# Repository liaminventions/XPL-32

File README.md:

# XPL-32

The XPL-32 is a homebrew 8-bit 6502 laptop, with four 48-pin expansion slots, and a 22-pin I/O port.
 ### XPL-32 stands for:
e**X**pandable 
**P**ersonal 
**L**aptop 
with **32**k ram
# [Blog](https://unstinkableinventions.wordpress.com/)
Here I will post hardware updates to the XPL and more.

Also, be sure to check info.txt to know if there are any issues when i code.
# Hardware Overview
## CPU
A 6502, of course. A W65C02 to be exact. 

[Datasheet](https://eater.net/datasheets/w65c02s.pdf)
## I/O
For the I/O, I've got a W65C22 VIA. Port A, Port B and the handshake bits connect to the I/O slot.
However CA2 is connected to the Video Switch Relay (VSR)
[W65C22 Datasheet](https://eater.net/datasheets/w65c22.pdf)
## Video
The XPL-32 has an expandable monochrome terminal display that uses a 6551 ACIA  at $8000 and two arduinos.
[This is the video and keyboard processer. (not made by me)](http://searle.x10host.com/MonitorKeyboard/index.html)
The video can be switched to the composite input EXTVID (on the expansion port) by toggling the VSR. (a relay that switches beetween native video and EXTVID.)

So far, for Video expansions, I've made a TMS9918a one. (the same video processer used in the TI-99/4a and the MSX)
## Sound
There is a 6581 SID at $B800 ($D400 in the c64) onboard with its potentiometer (POTX and POTY) and external sound (EXTSND) inputs on the expansion port.
I programmed support to convert most SID files, as well.
# Memory Map

# Tools I Use
## PCB Design
I currently use [EAGLE](https://www.autodesk.com/products/eagle/free-download)
## 3D Modeling
[Fusion 360](https://www.autodesk.com/products/fusion-360/overview?us_oa=dotcom-us&us_si=4e5471dc-07ed-4416-80c0-6f3e9f7c15b4&us_pt=NINVFUS&us_at=%5Bobject%20Object%5D&term=1-YEAR&tab=subscription&plc=F360)
## Coding
[VIM](https://www.vim.org/), [NVIM](https://neovim.io/)/[LunarVIM](https://www.lunarvim.org/) or [vscode](https://code.visualstudio.com/) for code editing.
[xa](https://github.com/fachat/xa65), [ca65](https://github.com/cc65/cc65) (from cc65), and [vasm](http://sun.hasenbraten.de/vasm/) for assembly.

I have "xa 6502 cross assembler" syntax highlighting in vim, and the "vasm" extension in vscode.

most source files are .s, but some are .a65 or .asm

## Debugging 

I use [Pulseview](https://sigrok.org/wiki/PulseView) with [this logic analyzer (the 2018 variant)](https://sigrok.org/wiki/Mcupro_Logic16_clone)

It was an absolute pain to set up...

Also, the SDcard-SPI decoder in libsigrokdecode was completly broken for me. (it always expected a CRC...) My fix was to make [my own custom version of the decoder](https://github.com/liaminventions/XPL-32/tree/main/debug/decoders/sdcard_spi)

The custom version is still slightly broken, but I am working on it.

I also use [decode6502 by hoglet](https://github.com/hoglet67/6502Decoder)

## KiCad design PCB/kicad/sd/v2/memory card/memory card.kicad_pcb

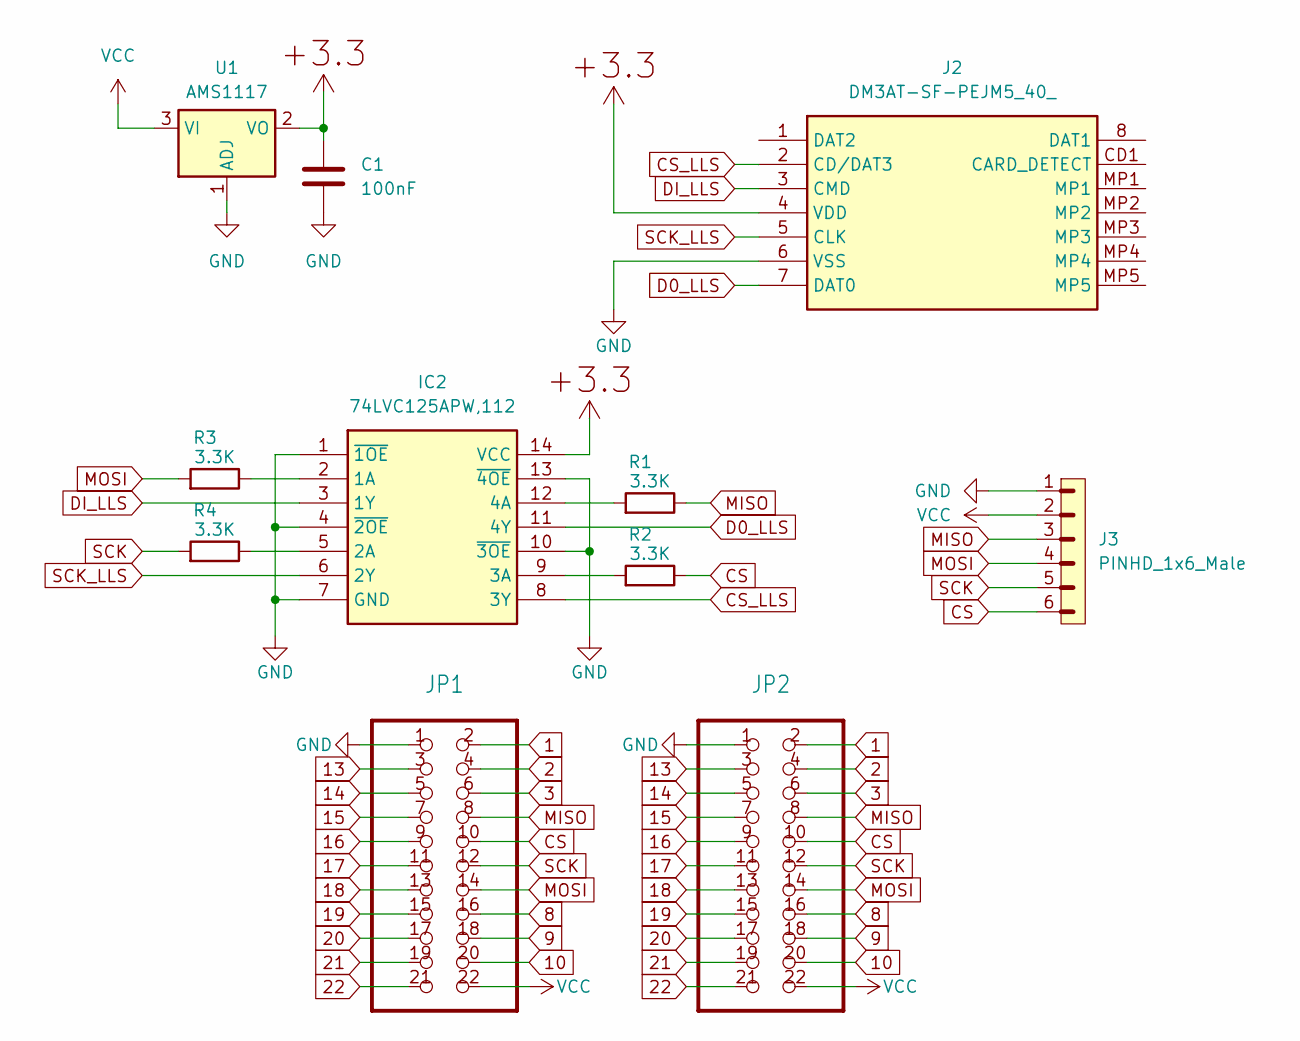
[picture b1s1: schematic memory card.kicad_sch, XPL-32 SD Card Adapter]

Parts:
C1: 100nF; C_0603_1608Metric
IC2: 74LVC125APW,112; SOP65P640X110-14N; Mouser2 Part Number 771-LVC125APW112
J2: DM3AT-SF-PEJM5_40_; DM3ATSFPEJM540; Mouser Part Number 798-DM3AT-SF-PEJM540
J3: PINHD_1x6_Male; PinHeader_1x06_P2.54mm_Vertical
JP1, JP2: 2X11_90_325
R1, R2, R3, R4: 3.3K; R_0805_2012Metric
U1: AMS1117; SOT-223-3_TabPin2

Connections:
1: JP1.2, JP2.2
2: JP1.4, JP2.4
3: JP1.6, JP2.6
8: JP1.16, JP2.16
9: JP1.18, JP2.18
10: JP1.20, JP2.20
13: JP1.3, JP2.3
14: JP1.5, JP2.5
15: JP1.7, JP2.7
16: JP1.9, JP2.9
17: JP1.11, JP2.11
18: JP1.13, JP2.13
19: JP1.15, JP2.15
20: JP1.17, JP2.17
21: JP1.19, JP2.19
22: JP1.21, JP2.21
CS: J3.6, JP1.10, JP2.10, R2.2
CS_LLS: IC2.8 (3Y), J2.2 (CD/DAT3)
D0_LLS: IC2.11 (4Y), J2.7 (DAT0)
DI_LLS: IC2.3 (1Y), J2.3 (CMD)
GND: C1.2, IC2.1 (~1OE), IC2.4 (~2OE), IC2.7 (GND), IC2.10 (~3OE), IC2.13 (~4OE), J2.6 (VSS), J3.1, JP1.1, JP2.1, U1.1 (ADJ)
MISO: J3.3, JP1.8, JP2.8, R1.2
MOSI: J3.4, JP1.14, JP2.14, R3.1
unnamed: IC2.2 (1A), R3.2
unnamed: IC2.5 (2A), R4.2
unnamed: IC2.9 (3A), R2.1
unnamed: IC2.12 (4A), R1.1
P,+3.3: C1.1, IC2.14 (VCC), J2.4 (VDD), U1.2 (VO)
SCK: J3.5, JP1.12, JP2.12, R4.1
SCK_LLS: IC2.6 (2Y), J2.5 (CLK)
VCC: J3.2, JP1.22, JP2.22, U1.3 (VI)

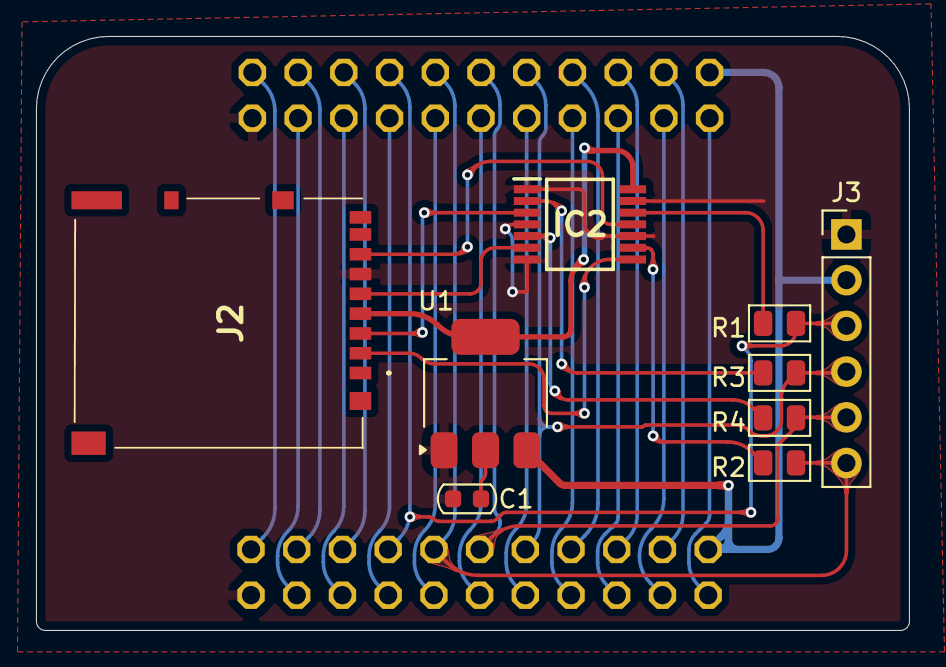
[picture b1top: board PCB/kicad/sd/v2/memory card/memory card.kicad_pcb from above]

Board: 2 copper layers, 48.5 x 33.0 mm, 11 parts (0 on the bottom side), 31 nets.

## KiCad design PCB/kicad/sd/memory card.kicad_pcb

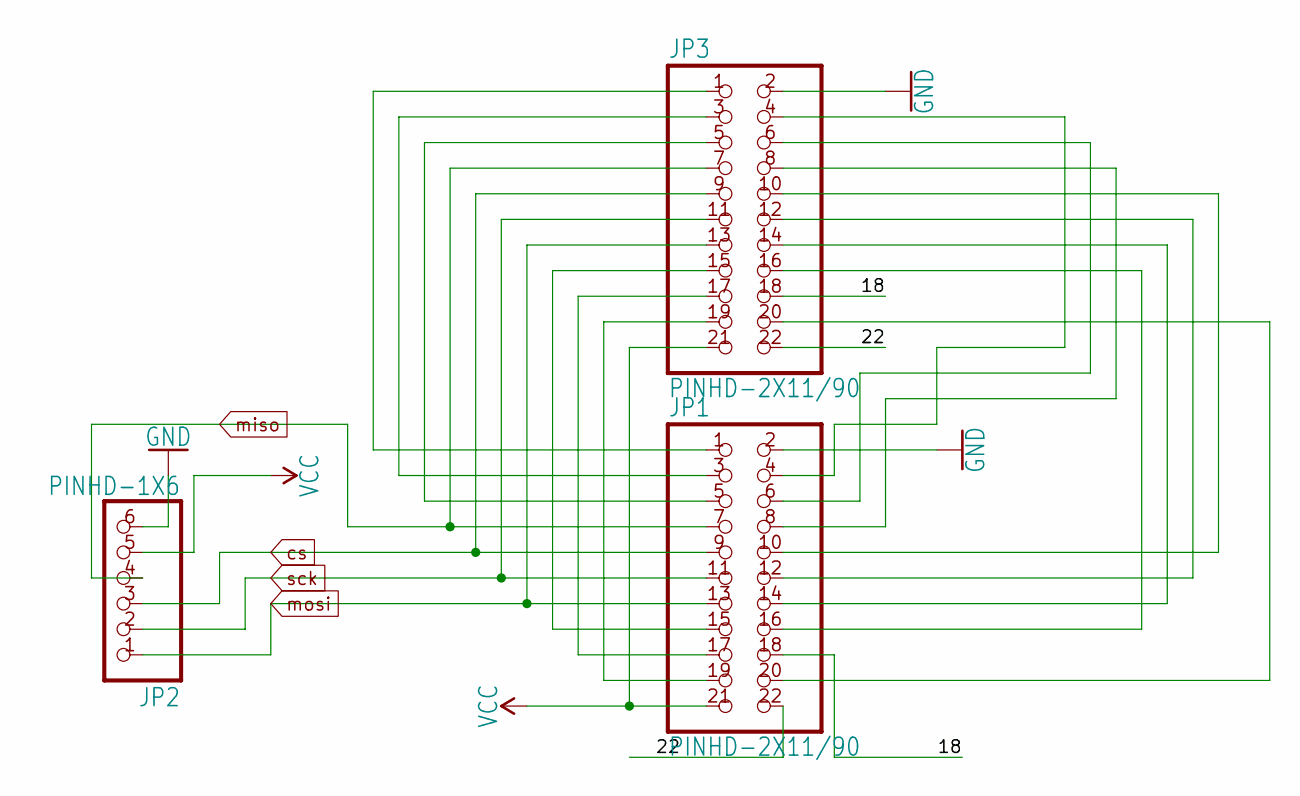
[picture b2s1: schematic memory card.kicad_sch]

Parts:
JP1, JP3: PINHD-2X11/90; 2X11_90
JP2: PINHD-1X6; 1X06

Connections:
18: JP1.18, JP3.18
22: JP1.22, JP3.22
GND: JP1.2, JP2.6, JP3.2
unnamed: JP1.20, JP3.20
unnamed: JP1.16, JP3.16
unnamed: JP1.14, JP3.14
unnamed: JP1.8, JP3.8
unnamed: JP1.19, JP3.19
unnamed: JP1.17, JP3.17
unnamed: JP1.15, JP3.15
unnamed: JP1.13, JP2.1, JP3.13
unnamed: JP1.11, JP2.2, JP3.11
unnamed: JP1.9, JP2.3, JP3.9
unnamed: JP1.7, JP2.4, JP3.7
unnamed: JP1.5, JP3.5
unnamed: JP1.3, JP3.3
unnamed: JP1.1, JP3.1
unnamed: JP1.6, JP3.6
unnamed: JP1.4, JP3.4
unnamed: JP1.12, JP3.12
unnamed: JP1.10, JP3.10
VCC: JP1.21, JP2.5, JP3.21

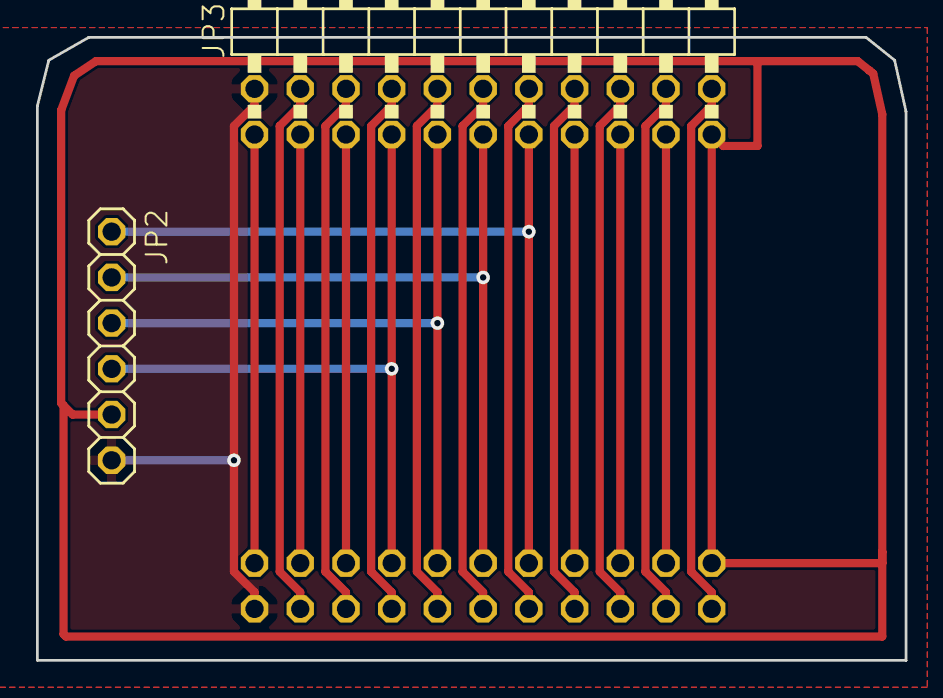
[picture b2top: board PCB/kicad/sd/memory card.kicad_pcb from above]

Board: 2 copper layers, 48.3 x 34.6 mm, 3 parts (1 on the bottom side), 22 nets.

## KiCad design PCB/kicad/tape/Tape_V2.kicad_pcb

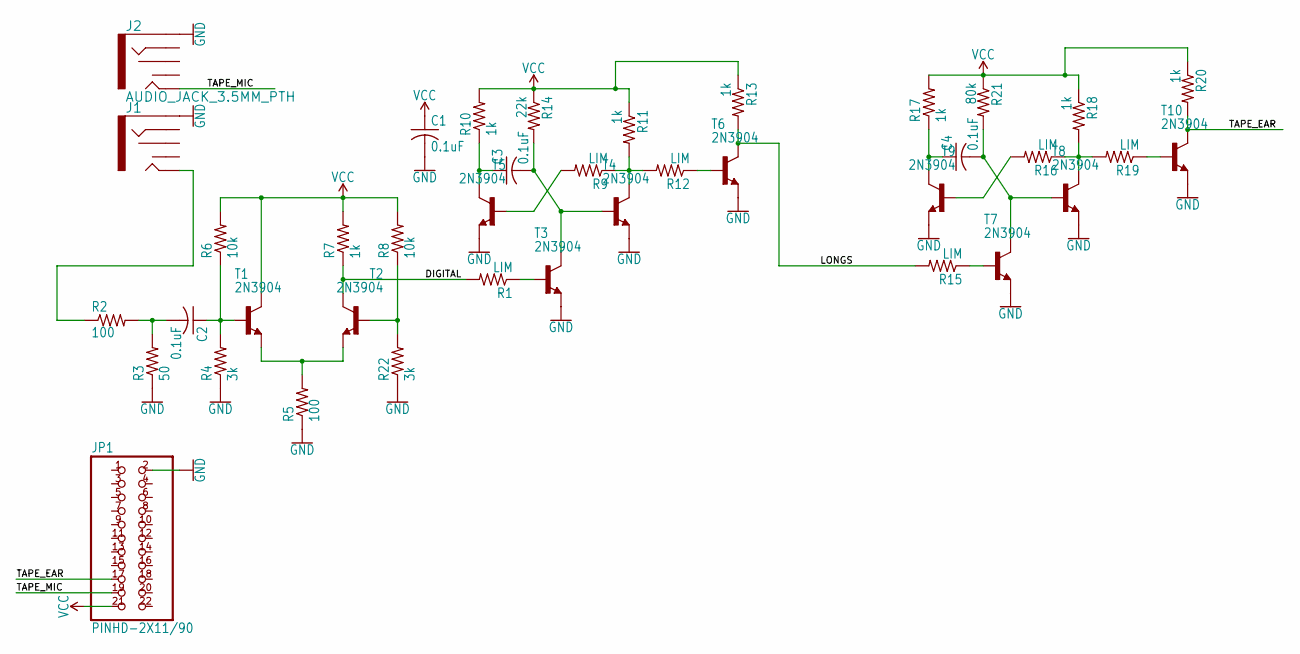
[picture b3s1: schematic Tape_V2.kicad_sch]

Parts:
C1, C2, C3, C4: 0.1uF; C025-030X050
J1, J2: AUDIO_JACK_3.5MM_PTH; AUDIO-JACK
JP1: PINHD-2X11/90; 2X11_90
R1, R9, R12, R15, R16, R19: LIM; 0204_7
R2, R5: 100; 0204_7
R3: 50; 0204_7
R4, R22: 3k; 0204_7
R6, R8: 10k; 0204_7
R7, R10, R11, R13, R17, R18, R20: 1k; 0204_7
R14: 22k; 0204_7
R21: 80k; 0204_7
T1, T2, T3, T4, T5, T6, T7, T8, T9, T10: 2N3904; TO92

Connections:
DIGITAL: R1.2, R7.1, T2.1 (C)
GND: C1.2, J1.SLEEVE, J2.SLEEVE, JP1.2, R3.1, R4.1, R5.1, R22.1, T3.3 (E), T4.3 (E), T5.3 (E), T6.3 (E), T7.3 (E), T8.3 (E), T9.3 (E), T10.3 (E)
LONGS: R13.2, R15.2, T6.1 (C)
unnamed: R5.2, T1.3 (E), T2.3 (E)
unnamed: C2.1, R4.2, R6.1, T1.2 (B)
unnamed: C2.2, R2.2, R3.2
unnamed: R1.1, T3.2 (B)
unnamed: R8.1, R22.2, T2.2 (B)
unnamed: J1.TIP, R2.1
unnamed: C3.2, R14.2, T3.1 (C), T4.2 (B)
unnamed: R9.2, T5.2 (B)
unnamed: C3.1, R10.1, T5.1 (C)
unnamed: R9.1, R11.2, R12.2, T4.1 (C)
unnamed: R12.1, T6.2 (B)
unnamed: R15.1, T7.2 (B)
unnamed: C4.2, R21.2, T7.1 (C), T8.2 (B)
unnamed: R16.2, T9.2 (B)
unnamed: C4.1, R17.1, T9.1 (C)
unnamed: R16.1, R18.2, R19.2, T8.1 (C)
unnamed: R19.1, T10.2 (B)
TAPE_EAR: JP1.17, R20.2, T10.1 (C)
TAPE_MIC: J2.TIP, JP1.19
VCC: C1.1, JP1.21, R6.2, R7.2, R8.2, R10.2, R11.1, R13.1, R14.1, R17.2, R18.1, R20.1, R21.1, T1.1 (C)

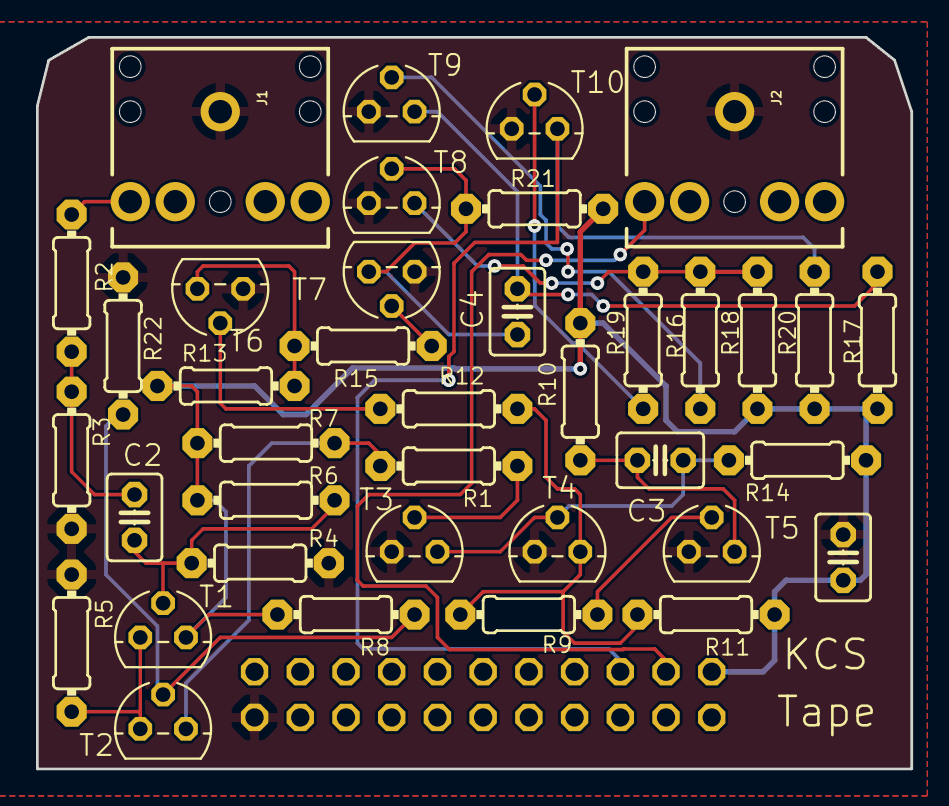
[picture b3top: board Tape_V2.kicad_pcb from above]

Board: 2 copper layers, 48.6 x 40.6 mm, 39 parts (1 on the bottom side), 23 nets.

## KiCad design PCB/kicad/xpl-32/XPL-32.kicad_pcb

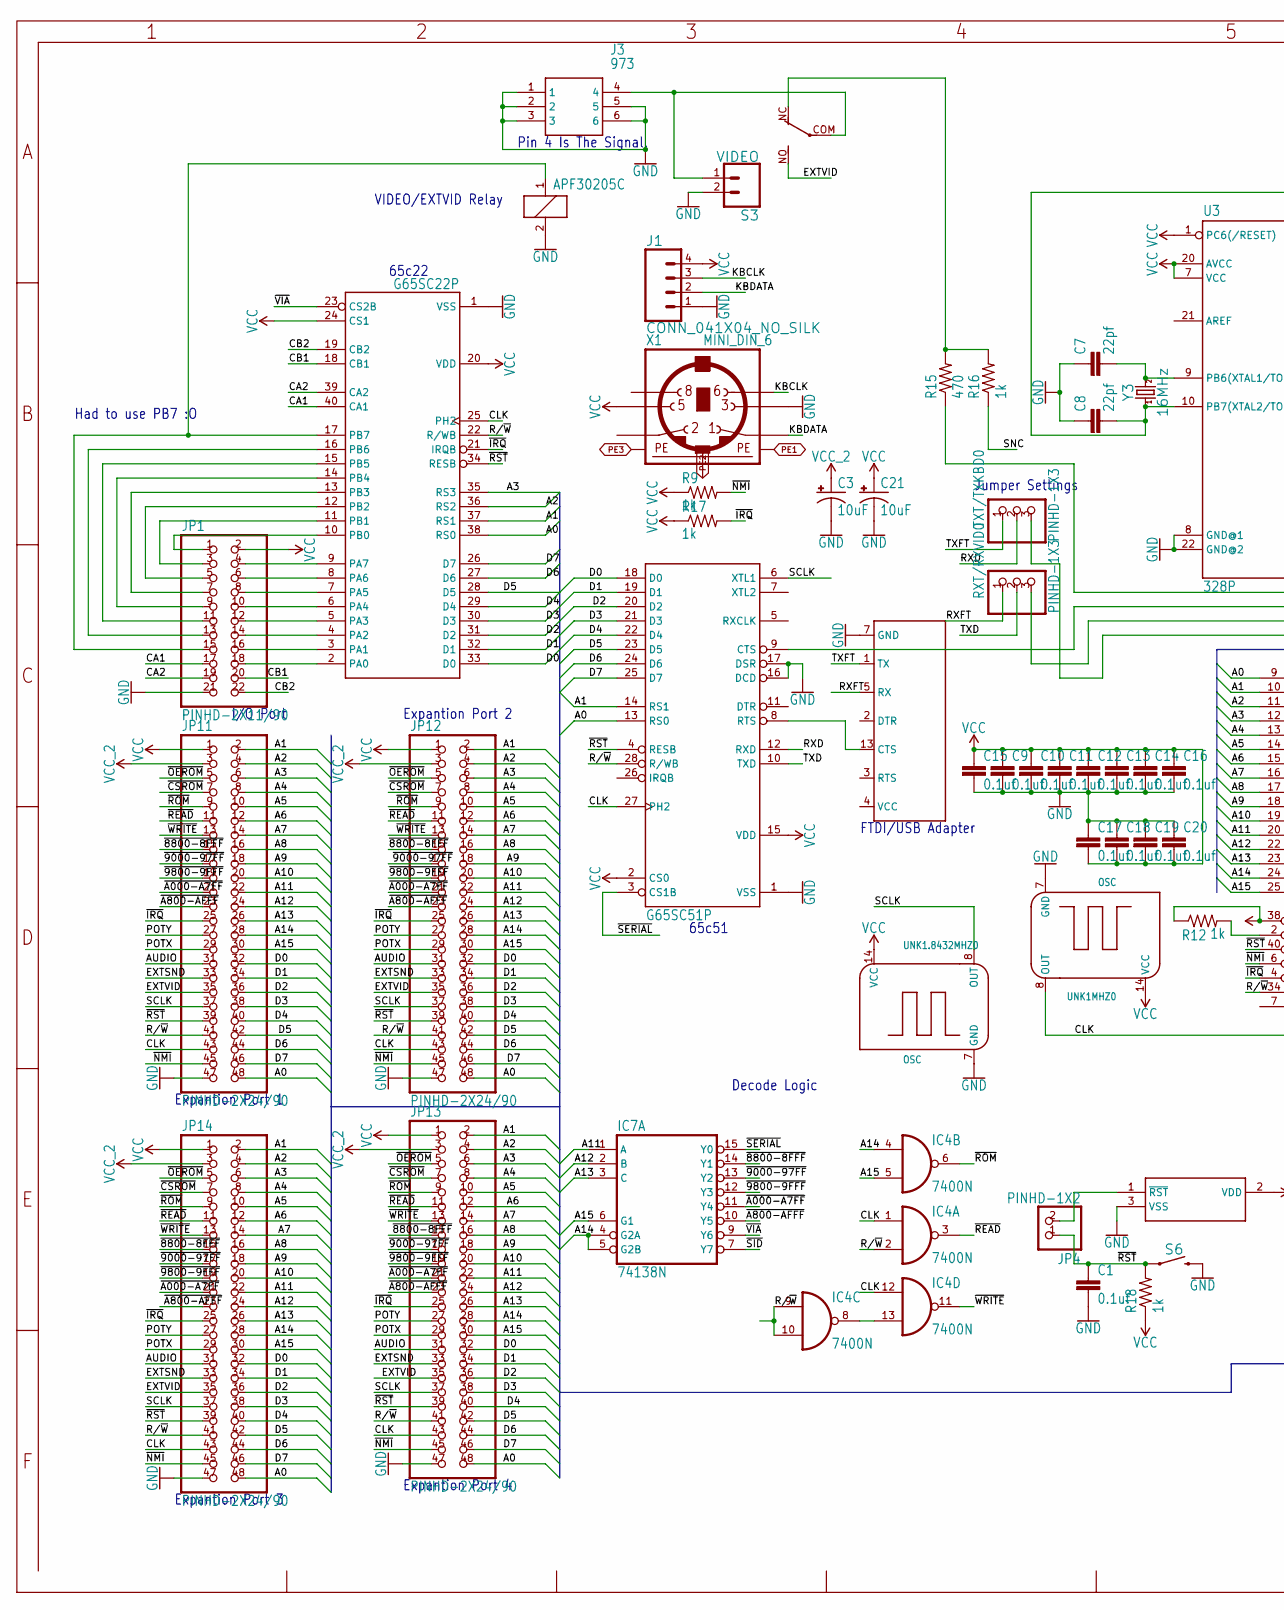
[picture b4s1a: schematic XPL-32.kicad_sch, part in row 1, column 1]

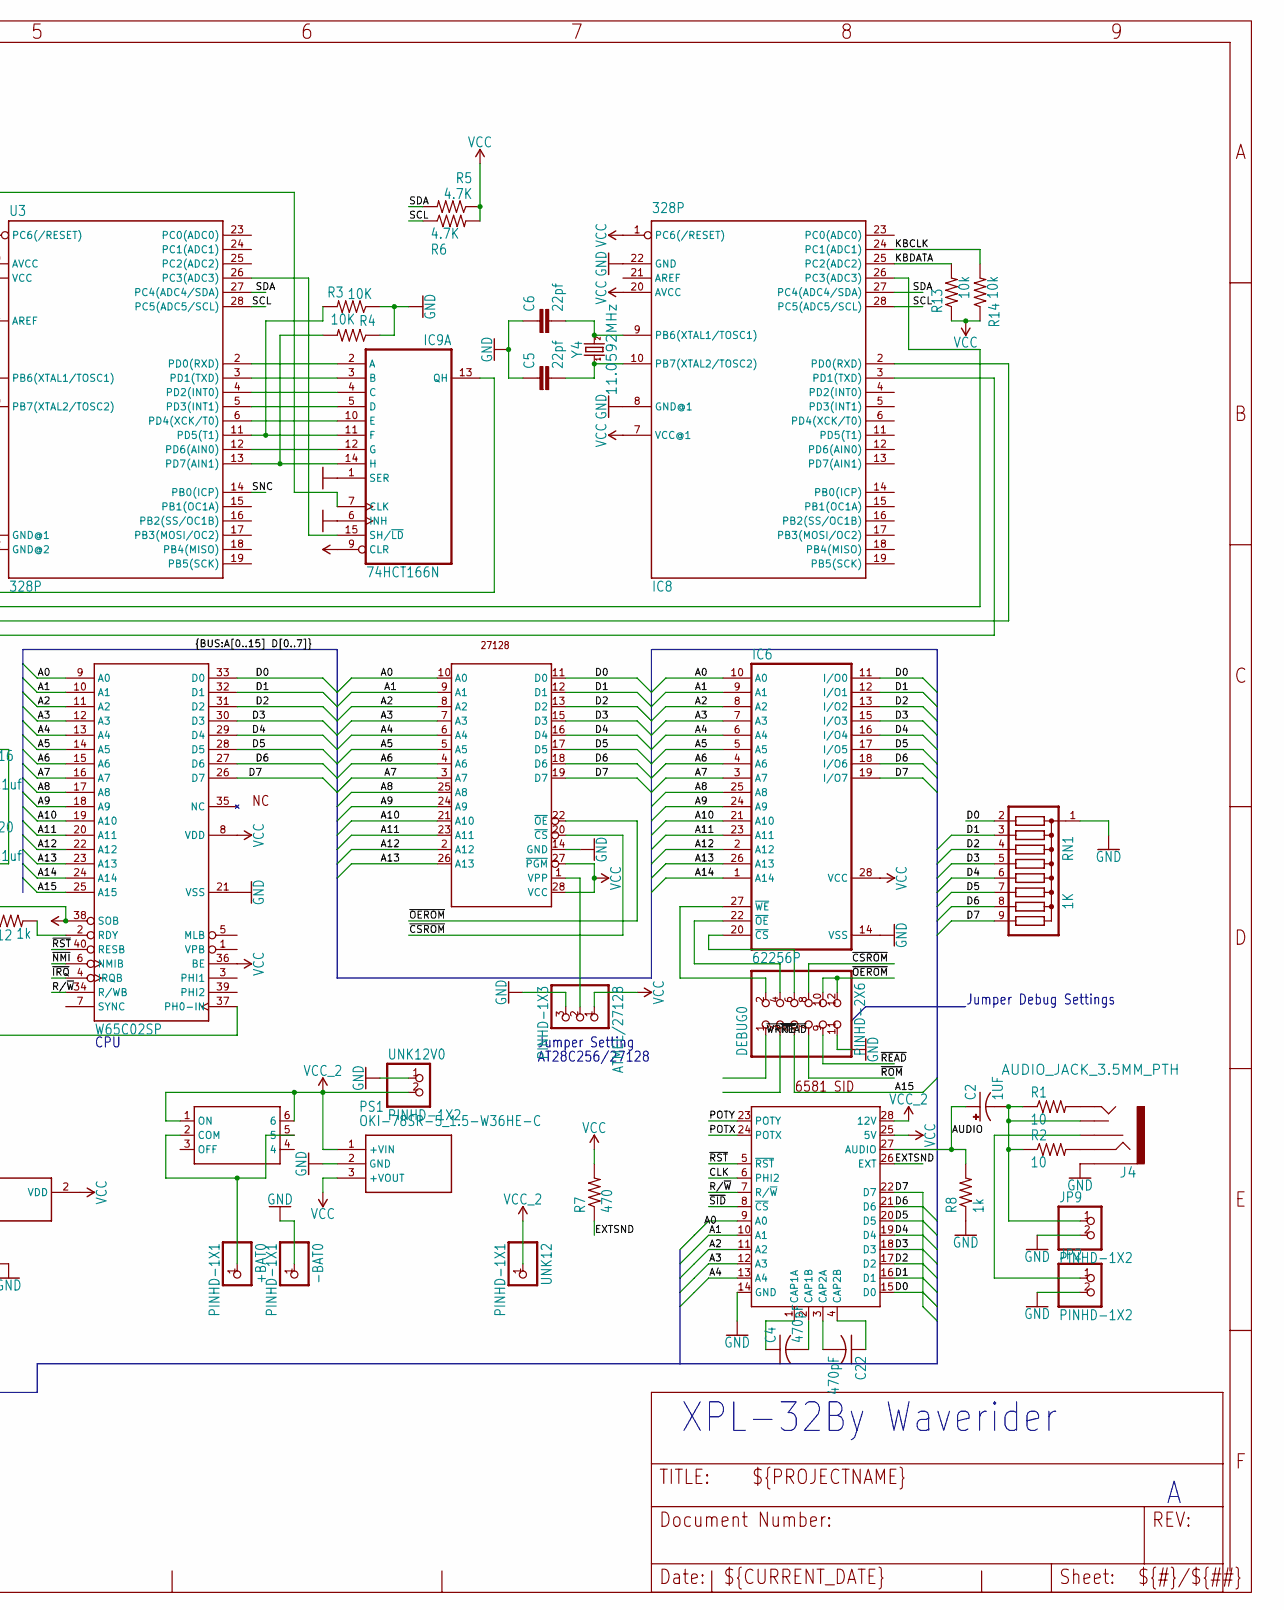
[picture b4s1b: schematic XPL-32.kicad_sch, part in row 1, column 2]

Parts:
+BAT0: PINHD-1X1; 1X01
-BAT0: PINHD-1X1; 1X01
ATMEL/27128: PINHD-1X3; 1X03
C1, C9, C10, C11, C12, C13, C14, C15, C16, C17, C18, C19, C20: 0.1uf; C025-025X050
C2: 1UF; E2,5-7
C3, C21: 10uF; E2,5-7
C4, C22: 470pF; C150-054X183
C5, C6, C7, C8: 22pf; C025-025X050
DEBUG0: PINHD-2X6; 2X06
IC4: 7400N; DIL14
IC6: 62256P; DIL28-6
IC7: 74138N; DIL16
IC8: 328P; DIL28-3
IC9: 74HCT166N; DIL16
IC10: MCP120-450DI_TO; TO127P254X495-3
J1: CONN_041X04_NO_SILK; 1X04_NO_SILK
J3: 973
J4: AUDIO_JACK_3.5MM_PTH; AUDIO-JACK
JP1: PINHD-2X11/90; 2X11_90
JP2, JP4, JP9: PINHD-1X2; 1X02
JP11, JP12, JP13, JP14: PINHD-2X24/90; 2X24_90
K1: APF30205C; APF30212C
PS1: OKI-78SR-5_1.5-W36HE-C; OKI78SR515W36HEC
R1, R2: 10; 0204_7
R3, R4: 10K; 0204_7
R5, R6: 4.7K; 0204_7
R7, R15: 470; 0204_7
R8, R9, R12, R16, R17, R18: 1k; 0204_7
R13, R14: 10k; 0204_7
RN1: 1K; SIL9
RXT/RXVID0: PINHD-1X3; 1X03
S3: VIDEO; 1X02_NO_SILK
S6: MOMENTARY-SWITCH-SPST-PTH-6.0MM; TACTILE_SWITCH_PTH_6.0MM
TXT/TXKBD0: PINHD-1X3; 1X03
U1: W65C02SP; DIP-40
U2: G65SC51P; DIP-28
U3: 328P; DIP28
U4: G65SC22P; DIP-40
U6: FTDI
U7: AT28C256/27128; DIP-28
U$1: TOGGLE_PUSHBUTTON; TOGGLE_BUTTON
U$2: 6581; DIP-28
UNK1.8432MHZ0, UNK1MHZ0: OSC; OSCCAN
UNK12: PINHD-1X1; 1X01
UNK12V0: PINHD-1X2; 1X02
X1: MINI_DIN_6; M_DIN6
Y3: 16MHz; HC49U
Y4: 11.0592MHz; HC49U

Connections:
A0: IC6.10 (A0), JP11.48, JP12.48, JP13.48, JP14.48, U1.9 (A0), U2.13 (RS0), U4.38 (RS0), U7.10 (A0), U$2.9 (A0)
A1: IC6.9 (A1), JP11.2, JP12.2, JP13.2, JP14.2, U1.10 (A1), U2.14 (RS1), U4.37 (RS1), U7.9 (A1), U$2.10 (A1)
A2: IC6.8 (A2), JP11.4, JP12.4, JP13.4, JP14.4, U1.11 (A2), U4.36 (RS2), U7.8 (A2), U$2.11 (A2)
A3: IC6.7 (A3), JP11.6, JP12.6, JP13.6, JP14.6, U1.12 (A3), U4.35 (RS3), U7.7 (A3), U$2.12 (A3)
A4: IC6.6 (A4), JP11.8, JP12.8, JP13.8, JP14.8, U1.13 (A4), U7.6 (A4), U$2.13 (A4)
A5: IC6.5 (A5), JP11.10, JP12.10, JP13.10, JP14.10, U1.14 (A5), U7.5 (A5)
A6: IC6.4 (A6), JP11.12, JP12.12, JP13.12, JP14.12, U1.15 (A6), U7.4 (A6)
A7: IC6.3 (A7), JP11.14, JP12.14, JP13.14, JP14.14, U1.16 (A7), U7.3 (A7)
A8: IC6.25 (A8), JP11.16, JP12.16, JP13.16, JP14.16, U1.17 (A8), U7.25 (A8)
A9: IC6.24 (A9), JP11.18, JP12.18, JP13.18, JP14.18, U1.18 (A9), U7.24 (A9)
A10: IC6.21 (A10), JP11.20, JP12.20, JP13.20, JP14.20, U1.19 (A10), U7.21 (A10)
A11: IC6.23 (A11), IC7.1 (A), JP11.22, JP12.22, JP13.22, JP14.22, U1.20 (A11), U7.23 (A11)
A12: IC6.2 (A12), IC7.2 (B), JP11.24, JP12.24, JP13.24, JP14.24, U1.22 (A12), U7.2 (A12)
A13: IC6.26 (A13), IC7.3 (C), JP11.26, JP12.26, JP13.26, JP14.26, U1.23 (A13), U7.26 (A13)
A14: IC4.4 (I0), IC6.1 (A14), IC7.4 (G2A), IC7.5 (G2B), JP11.28, JP12.28, JP13.28, JP14.28, U1.24 (A14)
A15: DEBUG0.5, IC4.5 (I1), IC7.6 (G1), JP11.30, JP12.30, JP13.30, JP14.30, U1.25 (A15)
AUDIO: C2.+, JP11.31, JP12.31, JP13.31, JP14.31, R8.2, U$2.27 (AUDIO)
CA1: JP1.17, U4.40 (CA1)
CA2: JP1.19, U4.39 (CA2)
CB1: JP1.20, U4.18 (CB1)
CB2: JP1.22, U4.19 (CB2)
CLK: IC4.1 (I0), IC4.12 (I0), JP11.43, JP12.43, JP13.43, JP14.43, U1.37 (PH0-IN), U2.27 (PH2), U4.25 (PH2), U$2.6 (PHI2), UNK1MHZ0.8 (OUT)
EXTSND: JP11.33, JP12.33, JP13.33, JP14.33, R7.1, U$2.26 (EXT)
EXTVID: JP11.35, JP12.35, JP13.35, JP14.35, K1.NO (S)
GND: -BAT0.1, ATMEL/27128.3, C1.2, C3.-, C5.1, C6.1, C7.1, C8.1, C9.2, C10.2, C11.2, C12.2, C13.2, C14.2, C15.2, C16.2, C17.1, C18.1, C19.1, C20.1, C21.-, DEBUG0.11, IC4.7 (GND), IC6.14 (VSS), IC7.8 (GND), IC8.8 (GND@1), IC8.22 (GND), IC9.1 (SER), IC9.6 (INH), IC9.8 (GND), IC10.3 (VSS), J1.1, J3.1, J3.2, J3.3, J3.5, J3.6, J4.SLEEVE, JP1.21, JP2.2, JP9.2, JP11.47, JP12.47, JP13.47, JP14.47, K1.2, PS1.2 (GND), R3.1, R4.1, R8.1, RN1.1, S3.2, S6.3 (2), U1.21 (VSS), U2.1 (VSS), U2.16 (DCD), U2.17 (DSR), U3.8 (GND@1), U3.22 (GND@2), U4.1 (VSS), U6.7 (GND), U7.14 (GND), U$2.14 (GND), UNK1.8432MHZ0.7 (GND), UNK1MHZ0.7 (GND), UNK12V0.1, X1.3
KBCLK: IC8.24 (PC1(ADC1)), J1.3, R14.2, X1.6
KBDATA: IC8.25 (PC2(ADC2)), J1.2, R13.2, X1.1
unnamed: ATMEL/27128.2, U7.1 (VPP)
unnamed: IC10.1 (~RST), JP4.2
unnamed: J4.RSH, JP2.1
unnamed: J4.TIP, R1.2
unnamed: +BAT0.1, U$1.2 (COM), U$1.5
unnamed: J4.RING, R2.2
unnamed: IC4.8 (O), IC4.13 (I1)
unnamed: JP1.1, U4.10 (PB0)
unnamed: DEBUG0.2, IC6.27 (~WE)
unnamed: IC8.2 (PD0(RXD)), RXT/RXVID0.3
unnamed: IC8.3 (PD1(TXD)), TXT/TXKBD0.3
unnamed: JP1.3, U4.11 (PB1)
unnamed: C2.-, J4.TSH, JP9.1, R1.1, R2.1
unnamed: JP1.5, U4.12 (PB2)
unnamed: JP1.15, K1.1, U4.17 (PB7)
unnamed: C22.2, U$2.3 (CAP2A)
unnamed: C4.2, U$2.2 (CAP1B)
unnamed: C22.1, U$2.4 (CAP2B)
unnamed: JP1.7, U4.13 (PB3)
unnamed: JP1.9, U4.14 (PB4)
unnamed: R12.2, U1.2 (RDY)
unnamed: C4.1, U$2.1 (CAP1A)
unnamed: U2.8 (RTS), U6.13 (CTS)
unnamed: JP1.11, U4.15 (PB5)
unnamed: C6.2, IC8.9 (PB6(XTAL1/TOSC1)), Y4.2
unnamed: C5.2, IC8.10 (PB7(XTAL2/TOSC2)), Y4.1
unnamed: C7.2, U3.9 (PB6(XTAL1/TOSC1)), Y3.2
unnamed: C8.2, IC9.7 (CLK), U3.10 (PB7(XTAL2/TOSC2)), Y3.1
unnamed: IC8.26 (PC3(ADC3)), U2.9 (CTS)
unnamed: IC9.15 (SH/~LD), U3.26 (PC3(ADC3))
unnamed: J3.4, K1.COM, S3.1
unnamed: JP1.13, U4.16 (PB6)
unnamed: K1.NC (O), R15.2, R16.2
unnamed: JP1.18, U4.2 (PA0)
unnamed: JP1.16, U4.3 (PA1)
unnamed: JP1.14, U4.4 (PA2)
unnamed: JP1.12, U4.5 (PA3)
unnamed: JP1.10, U4.6 (PA4)
unnamed: JP1.8, U4.7 (PA5)
unnamed: JP1.6, U4.8 (PA6)
unnamed: JP1.4, U4.9 (PA7)
unnamed: IC9.2 (A), U3.2 (PD0(RXD))
unnamed: IC9.3 (B), U3.3 (PD1(TXD))
unnamed: IC9.4 (C), U3.4 (PD2(INT0))
unnamed: IC9.5 (D), U3.5 (PD3(INT1))
unnamed: IC9.10 (E), U3.6 (PD4(XCK/T0))
unnamed: IC9.11 (F), R3.2, U3.11 (PD5(T1))
unnamed: IC9.12 (G), U3.12 (PD6(AIN0))
unnamed: IC9.14 (H), R4.2, U3.13 (PD7(AIN1))
unnamed: IC9.13 (QH), R15.1
unnamed: DEBUG0.4, IC6.22 (~OE)
unnamed: DEBUG0.6, IC6.20 (~CS)
PE1: X1.SH1 (PE1)
PE2: X1.SH2 (PE2)
PE3: X1.SH3 (PE3)
POTX: JP11.29, JP12.29, JP13.29, JP14.29, U$2.24 (POTX)
POTY: JP11.27, JP12.27, JP13.27, JP14.27, U$2.23 (POTY)
R/~W: IC4.2 (I1), IC4.9 (I0), IC4.10 (I1), JP11.41, JP12.41, JP13.41, JP14.41, U1.34 (R/WB), U2.28 (R/WB), U4.22 (R/WB), U$2.7 (R/~W)
RXD: TXT/TXKBD0.2, U2.12 (RXD)
RXFT: RXT/RXVID0.1, U6.5 (RX)
SCL: IC8.28 (PC5(ADC5/SCL)), R6.1, U3.28 (PC5(ADC5/SCL))
SCLK: JP11.37, JP12.37, JP13.37, JP14.37, U2.6 (XTL1), UNK1.8432MHZ0.8 (OUT)
SDA: IC8.27 (PC4(ADC4/SDA)), R5.2, U3.27 (PC4(ADC4/SDA))
SNC: R16.1, U3.14 (PB0(ICP))
TXD: RXT/RXVID0.2, U2.10 (TXD)
TXFT: TXT/TXKBD0.1, U6.1 (TX)
VCC: ATMEL/27128.1, C9.1, C10.1, C11.1, C12.1, C13.1, C14.1, C15.1, C16.1, C17.2, C18.2, C19.2, C20.2, C21.+, IC4.14 (VCC), IC6.28 (VCC), IC7.16 (VCC), IC8.1 (PC6(/RESET)), IC8.7 (VCC@1), IC8.20 (AVCC), IC9.9 (CLR), IC9.16 (VCC), IC10.2 (VDD), J1.4, JP1.2, JP11.1, JP12.1, JP13.1, JP14.1, PS1.3 (+VOUT), R5.1, R6.2, R7.2, R9.1, R12.1, R13.1, R14.1, R17.1, R18.1, U1.8 (VDD), U1.36 (BE), U1.38 (SOB), U2.2 (CS0), U2.15 (VDD), U3.1 (PC6(/RESET)), U3.7 (VCC), U3.20 (AVCC), U4.20 (VDD), U4.24 (CS1), U7.27 (~PGM), U7.28 (VCC), U$2.25 (5V), UNK1.8432MHZ0.14 (VCC), UNK1MHZ0.14 (VCC), X1.5
VCC_2: C3.+, JP11.3, JP12.3, JP13.3, JP14.3, PS1.1 (+VIN), U$1.1 (ON), U$1.6, U$2.28 (12V), UNK12.1, UNK12V0.2
~8800-8FFF: IC7.14 (Y1), JP11.15, JP12.15, JP13.15, JP14.15
~9000-97FF: IC7.13 (Y2), JP11.17, JP12.17, JP13.17, JP14.17
~9800-9FFF: IC7.12 (Y3), JP11.19, JP12.19, JP13.19, JP14.19
~A000-A7FF: IC7.11 (Y4), JP11.21, JP12.21, JP13.21, JP14.21
~A800-AFFF: IC7.10 (Y5), JP11.23, JP12.23, JP13.23, JP14.23
~CSROM: DEBUG0.8, JP11.7, JP12.7, JP13.7, JP14.7, U7.20 (~CS)
~IRQ: JP11.25, JP12.25, JP13.25, JP14.25, R17.2, U1.4 (IRQB), U4.21 (IRQB)
~NMI: JP11.45, JP12.45, JP13.45, JP14.45, R9.2, U1.6 (NMIB)
~OEROM: DEBUG0.10, DEBUG0.12, JP11.5, JP12.5, JP13.5, JP14.5, U7.22 (~OE)
~READ: DEBUG0.3, DEBUG0.9, IC4.3 (O), JP11.11, JP12.11, JP13.11, JP14.11
~ROM: DEBUG0.7, IC4.6 (O), JP11.9, JP12.9, JP13.9, JP14.9
~RST: C1.1, JP4.1, JP11.39, JP12.39, JP13.39, JP14.39, R18.2, S6.1, U1.40 (RESB), U2.4 (RESB), U4.34 (RESB), U$2.5 (~RST)
~SERIAL: IC7.15 (Y0), U2.3 (CS1B)
~SID: IC7.7 (Y7), U$2.8 (~CS)
~VIA: IC7.9 (Y6), U4.23 (CS2B)
~WRITE: DEBUG0.1, IC4.11 (O), JP11.13, JP12.13, JP13.13, JP14.13

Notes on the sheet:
AT28C256/27128
65c51
Expantion Port 3
Jumper Settings
Expantion Port 2
Had to use PB7 :O
Pin 4 Is The Signal.
65c22
XPL-32
Jumper Setting
Expantion Port 1
I/O Port
CPU
Decode Logic
By Waverider
Expantion Port 4
FTDI/USB Adapter
VIDEO/EXTVID Relay
Jumper Debug Settings

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
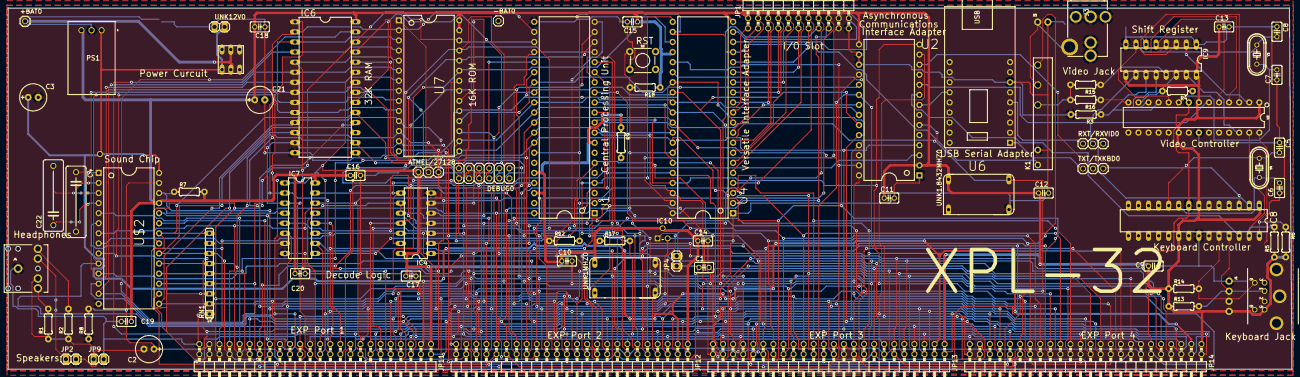
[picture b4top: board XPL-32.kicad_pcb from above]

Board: 2 copper layers, 323.8 x 91.1 mm, 81 parts (1 on the bottom side), 116 nets.
